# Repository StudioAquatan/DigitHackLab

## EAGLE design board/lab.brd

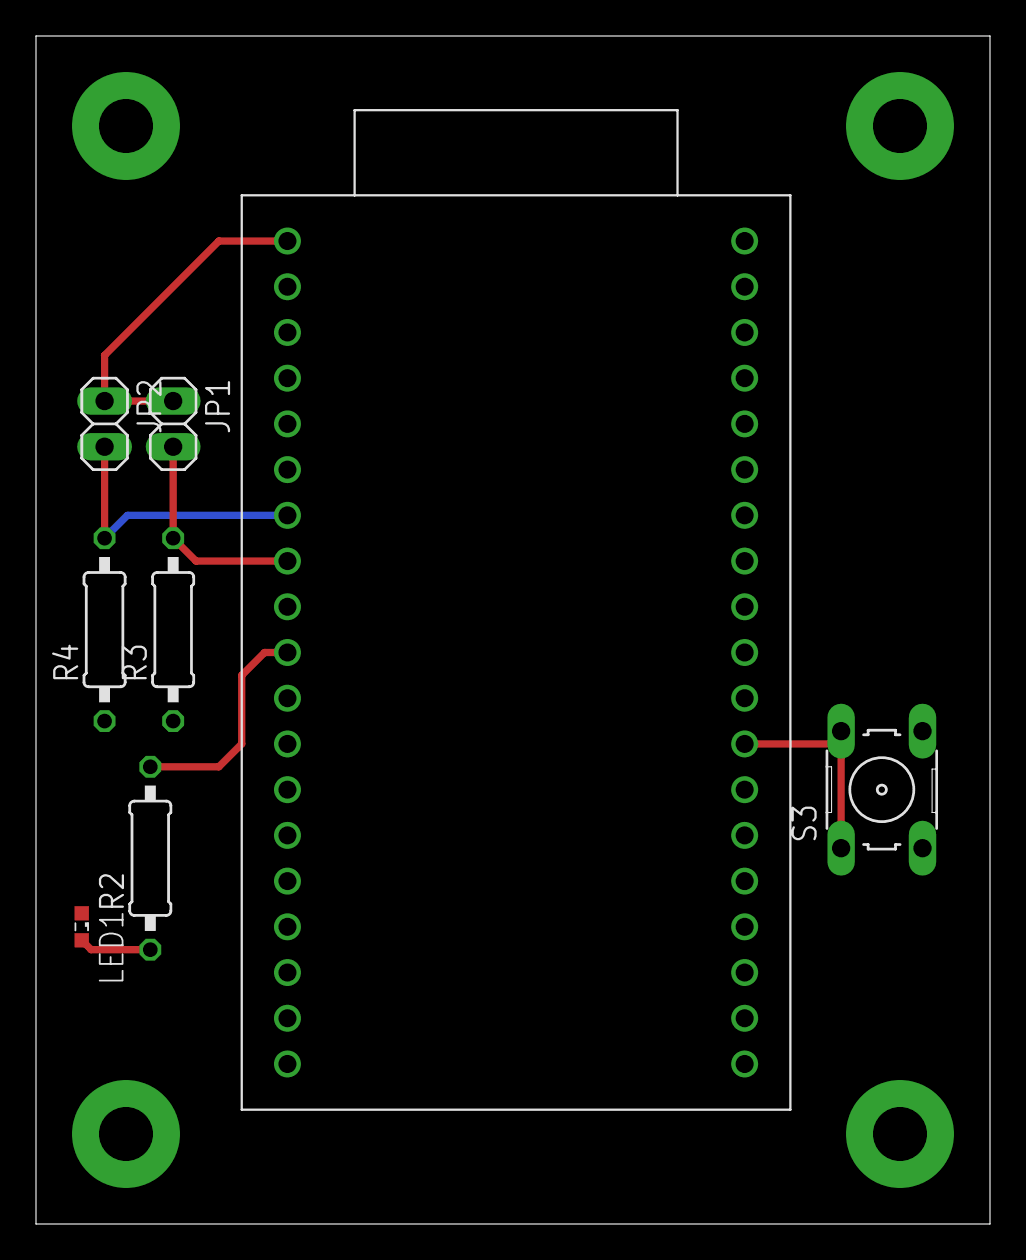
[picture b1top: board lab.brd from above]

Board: 2 copper layers, 53.0 x 66.0 mm, 8 parts (0 on the bottom side), 7 nets.

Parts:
JP1, JP2: 1X02
LED1: SML0603
R2: 1k; 0207/10
R3, R4: 10k; 0207/10
S3: B3F-10XX
U$1: ESP32_DEVKITC

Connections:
+3V3: JP1.1, JP2.1, U$1.P$19
+5V1: LED1.A, R2.1
A4: JP2.2, R4.2, U$1.P$13
A5: JP1.2, R3.2, U$1.P$12
GND: LED1.C, R3.1, R4.1, S3.3, S3.4, U$1.P$6, U$1.P$32, U$1.P$38
IO16: S3.1, S3.2, U$1.P$27
LED: R2.2, U$1.P$10

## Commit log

2018-05-25 add board
2018-05-25 add user_button
2018-05-25 change ADCpin A18 -> A4
2018-06-06 add arduino program
2018-06-08 fix path
2018-06-08 refactor
2018-06-08 ignore setting.h
2018-06-08 post処理を追加
2018-06-08 fix post
